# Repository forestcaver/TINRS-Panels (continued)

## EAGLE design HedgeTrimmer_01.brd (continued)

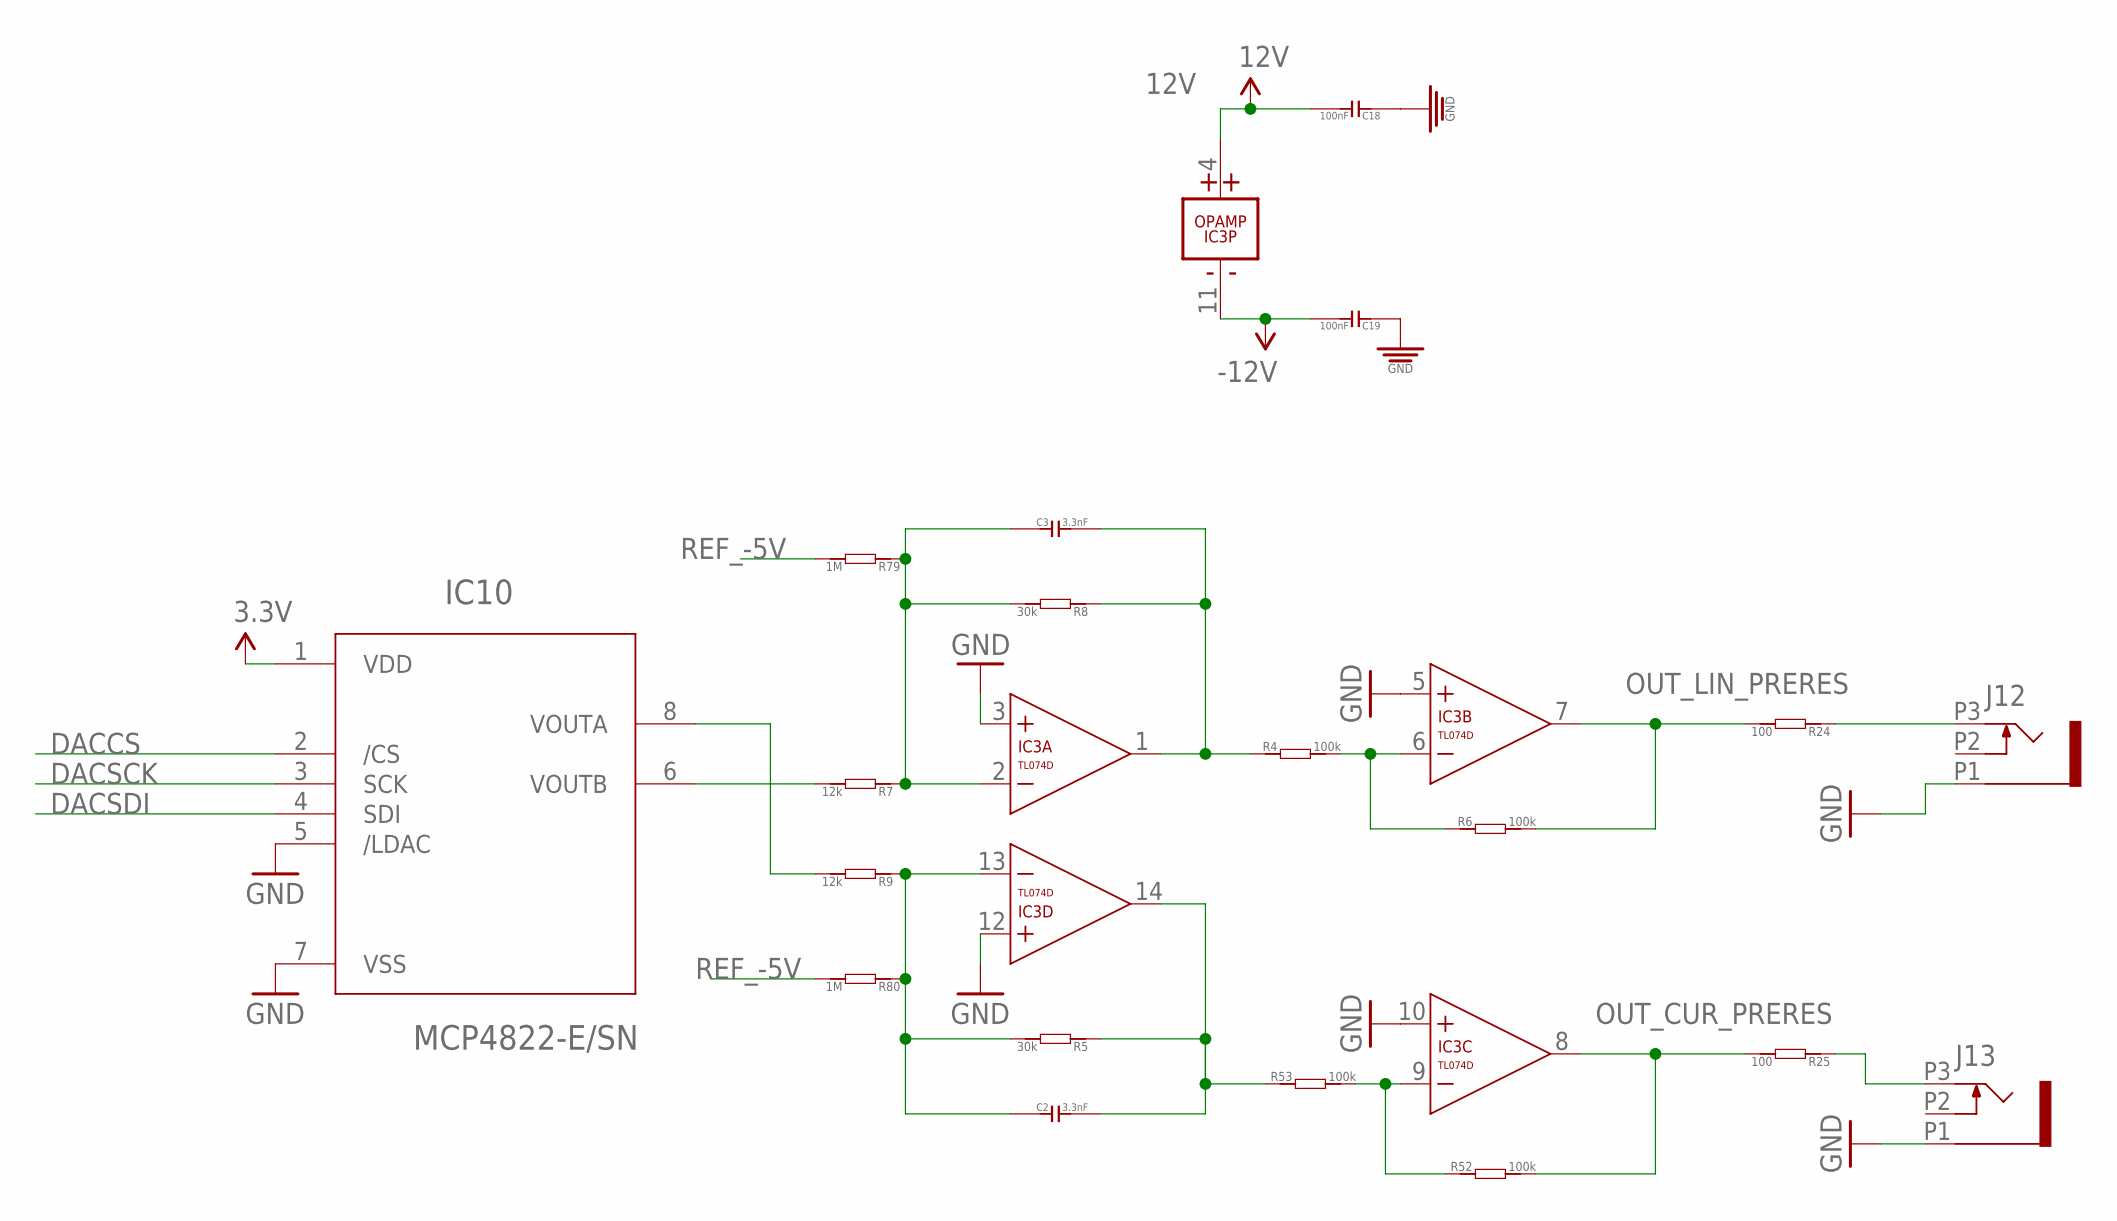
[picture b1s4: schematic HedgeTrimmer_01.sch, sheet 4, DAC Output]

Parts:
C2, C3: 3.3nF; C0603
C18, C19: 100nF; C0603; MPN MC0603F104Z160CT
IC3: TL074D; SO14; MPN TL074CD
IC10: MCP4822-E/SN; SOIC8-N_MC
J12, J13: PJ301_THONKICONN8; WQP_PJ_301M8
R4, R6, R52, R53: 100k; R0603
R5, R8: 30k; R0603
R7, R9: 12k; R0603
R24, R25: 100; R0603
R79, R80: 1M; R0603

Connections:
3.3V: IC10.1 (VDD); also elsewhere on the board
12V: C18.2, IC3.4 (V+); also elsewhere on the board
-12V: C19.2, IC3.11 (V-); also elsewhere on the board
DACA_INPUTSUMMER: C2.1, IC3.13 (-IN), R5.2, R9.1, R80.1
DACB_INPUTSUMMER: C3.1, IC3.2 (-IN), R7.1, R8.2, R79.1
DACCS: IC10.2 (/CS); also elsewhere on the board
DACSCK: IC10.3 (SCK); also elsewhere on the board
DACSDI: IC10.4 (SDI); also elsewhere on the board
GND: C18.1, C19.1, IC3.3 (+IN), IC3.5 (+IN), IC3.10 (+IN), IC3.12 (+IN), IC10.5 (/LDAC), IC10.7 (VSS), J12.P1 (1), J13.P1 (1); also elsewhere on the board
unnamed: IC3.6 (-IN), R4.2, R6.1
unnamed: IC10.8 (VOUTA), R9.2
unnamed: IC10.6 (VOUTB), R7.2
unnamed: J12.P3 (3), R24.1
unnamed: IC3.9 (-IN), R52.1, R53.2
unnamed: C3.2, IC3.1 (OUT), R4.1, R8.1
unnamed: J13.P3 (3), R25.1
unnamed: C2.2, IC3.14 (OUT), R5.1, R53.1
OUT_CUR_PRERES: IC3.8 (OUT), R25.2, R52.2; also elsewhere on the board
OUT_LIN_PRERES: IC3.7 (OUT), R6.2, R24.2
REF_-5V: R79.2, R80.2; also elsewhere on the board

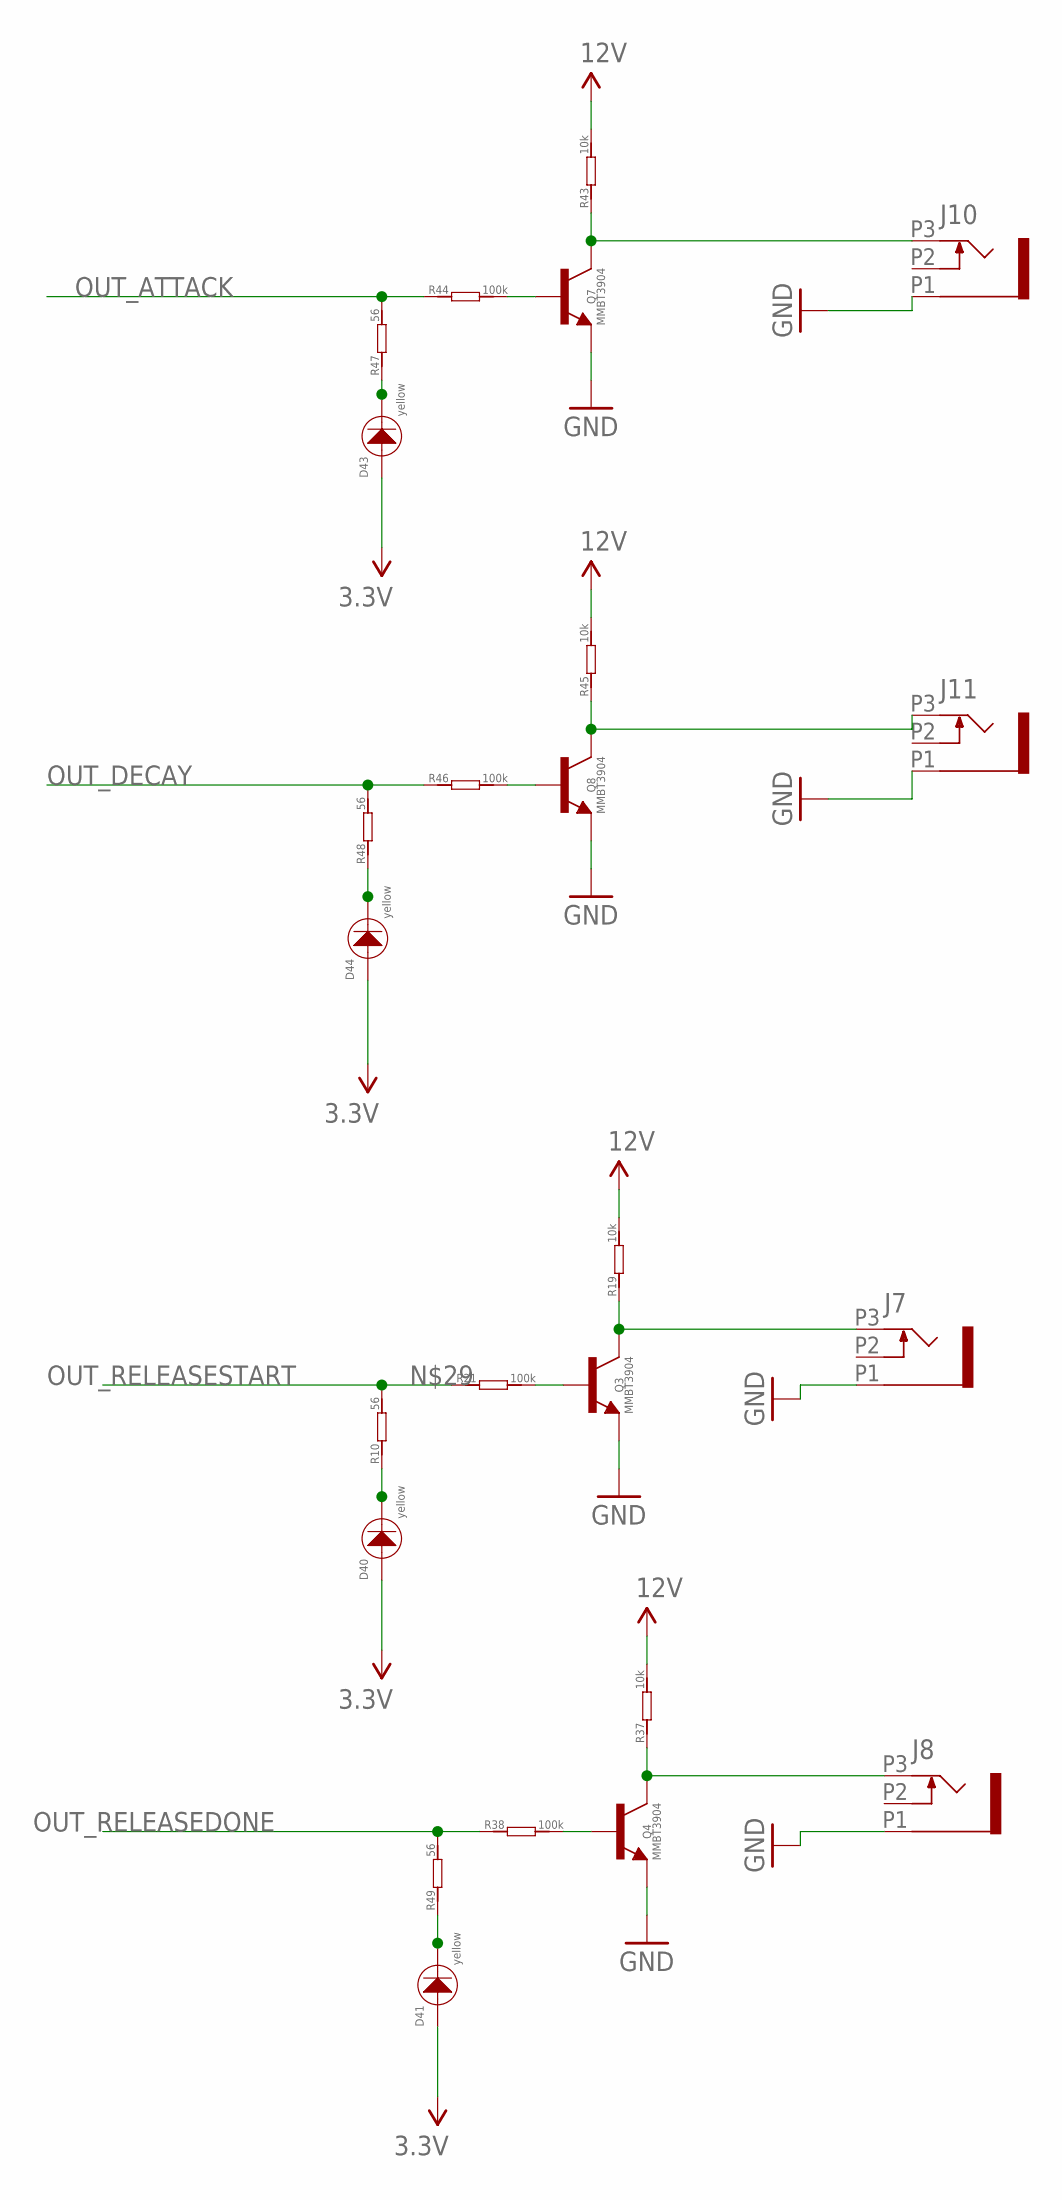
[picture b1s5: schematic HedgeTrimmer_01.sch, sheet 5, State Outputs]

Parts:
D40, D41, D43, D44: yellow; 3MMLED
J7, J8, J10, J11: PJ301_THONKICONN8; WQP_PJ_301M8
Q3, Q4, Q7, Q8: MMBT3904; SOT23-BEC; MPN PMBT3904,215
R10, R47, R48, R49: 56; R0603
R19, R37, R43, R45: 10k; R0603
R21, R38, R44, R46: 100k; R0603

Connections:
3.3V: D40.+, D41.+, D43.+, D44.+; also elsewhere on the board
12V: R19.2, R37.2, R43.2, R45.2; also elsewhere on the board
D21: D43.-, R47.1
GND: J7.P1 (1), J8.P1 (1), J10.P1 (1), J11.P1 (1), Q3.E, Q4.E, Q7.E, Q8.E; also elsewhere on the board
unnamed: D40.-, R10.1
unnamed: Q3.B, R21.2
unnamed: J7.P3 (3), Q3.C, R19.1
unnamed: D41.-, R49.1
unnamed: D44.-, R48.1
unnamed: Q4.B, R38.2
unnamed: J8.P3 (3), Q4.C, R37.1
unnamed: Q7.B, R44.2
unnamed: J10.P3 (3), Q7.C, R43.1
unnamed: Q8.B, R46.2
unnamed: J11.P3 (3), Q8.C, R45.1
OUT_ATTACK: R44.1, R47.2; also elsewhere on the board
OUT_DECAY: R46.1, R48.2; also elsewhere on the board
OUT_RELEASEDONE: R38.1, R49.2; also elsewhere on the board
OUT_RELEASESTART: R10.2, R21.1; also elsewhere on the board

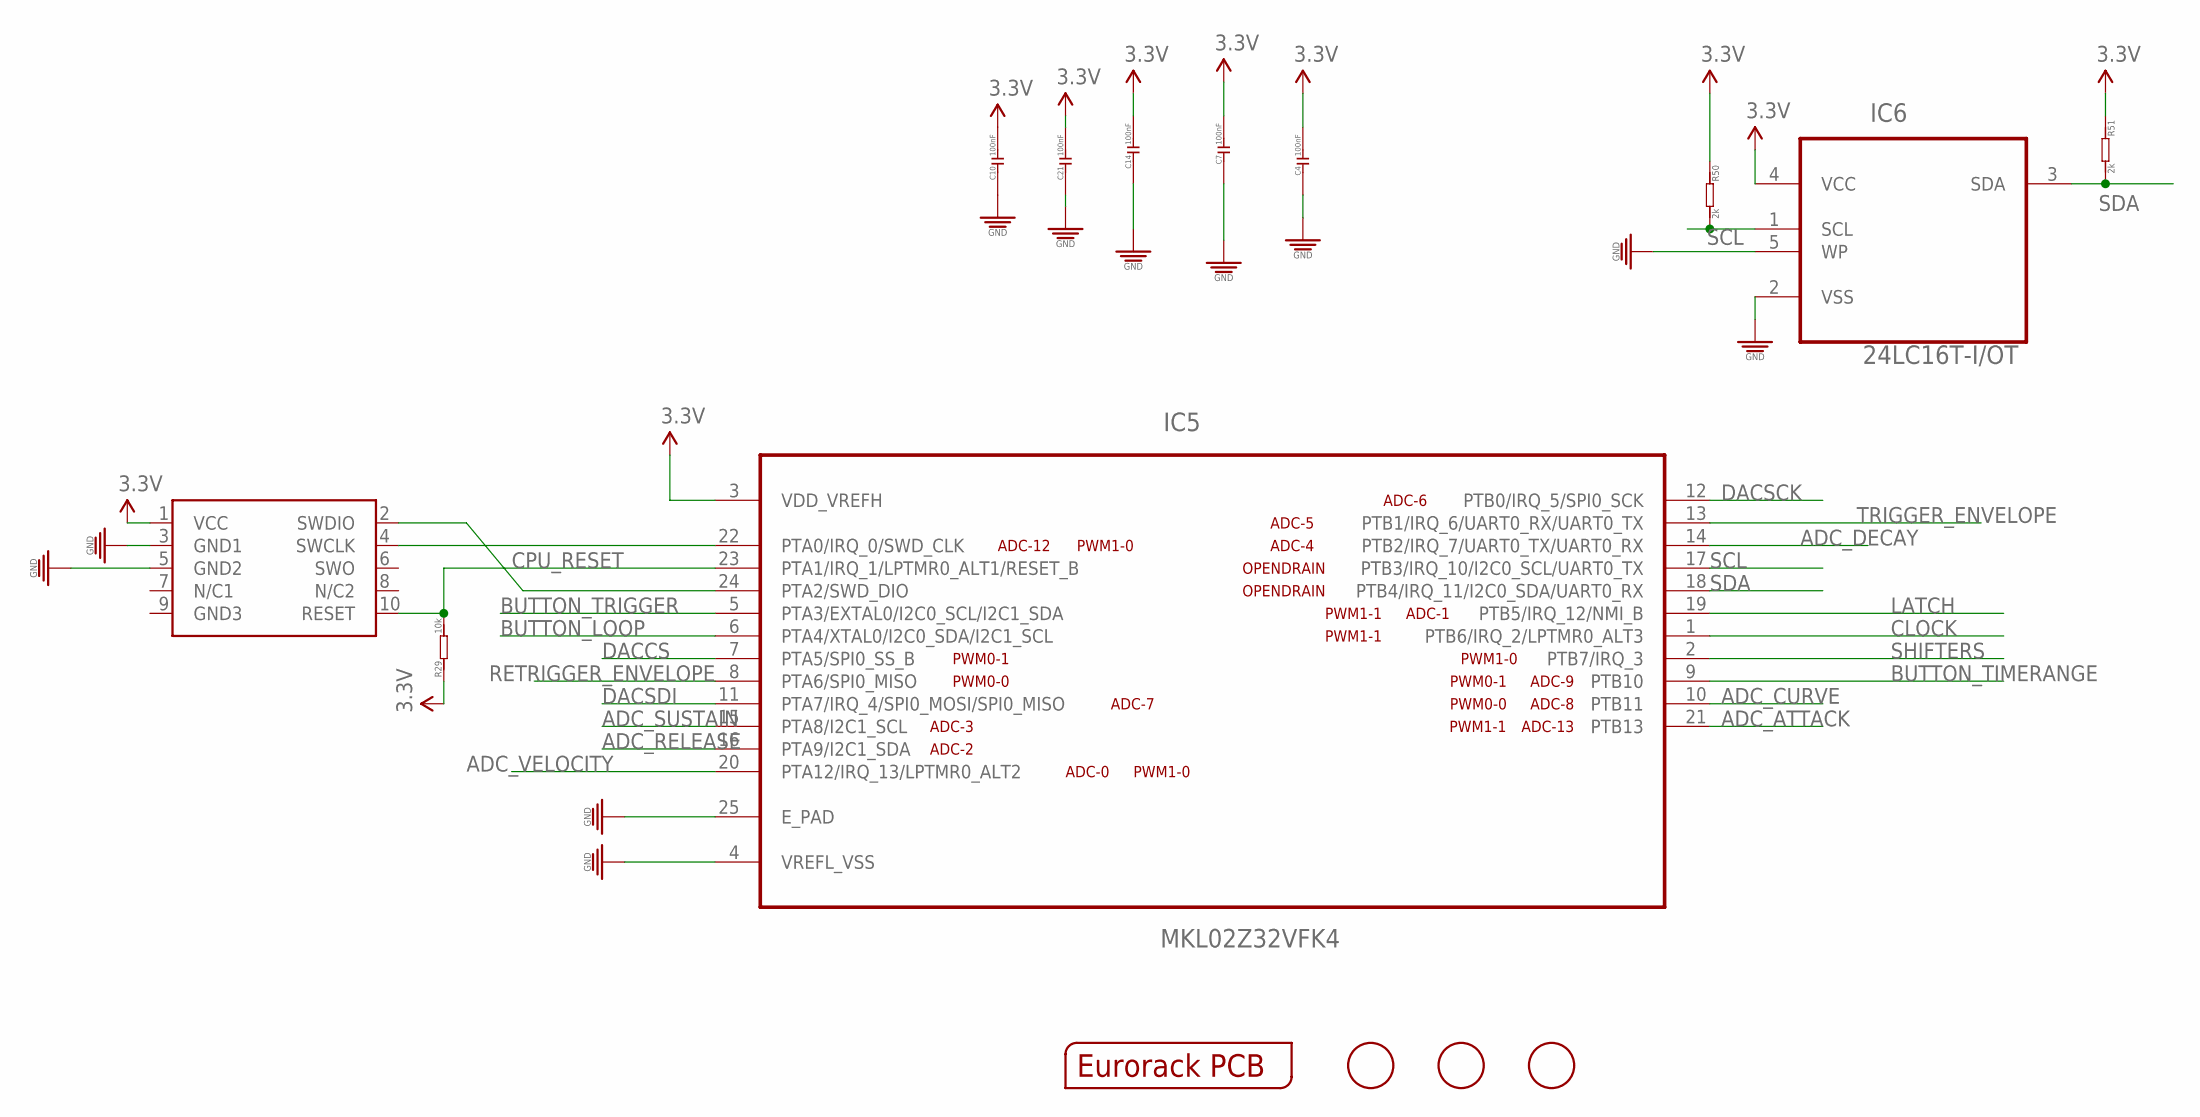
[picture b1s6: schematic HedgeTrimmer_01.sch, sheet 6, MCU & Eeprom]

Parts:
C4, C7, C10, C14, C21: 100nF; C0603; MPN MC0603F104Z160CT
FID1, FID2, FID3: FIDUCIAL; FIDUCIAL_1MM
IC5: MKL02Z32VFK4; QFN50P400X400X100-25N
IC6: 24LC16T-I/OT; SOT95P290X145-5N; MPN 24LC16T-I/OT
OUTLINE: EURORACK_PCB12HP; EURORACK12HPPCB
R29: 10k; R0603
R50, R51: 2k; R0603
SWD1: CORTEX_SWD; M50-3600542

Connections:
3.3V: C4.2, C7.2, C10.2, C14.2, C21.2, IC5.3 (VDD_VREFH), IC6.4 (VCC), R29.1, R50.1, R51.1, SWD1.1 (VCC); also elsewhere on the board
ADC_ATTACK: IC5.21 (PTB13); also elsewhere on the board
ADC_CURVE: IC5.10 (PTB11); also elsewhere on the board
ADC_DECAY: IC5.14 (PTB2/IRQ_7/UART0_TX/UART0_RX); also elsewhere on the board
ADC_RELEASE: IC5.16 (PTA9/I2C1_SDA); also elsewhere on the board
ADC_SUSTAIN: IC5.15 (PTA8/I2C1_SCL); also elsewhere on the board
ADC_VELOCITY: IC5.20 (PTA12/IRQ_13/LPTMR0_ALT2); also elsewhere on the board
BUTTON_LOOP: IC5.6 (PTA4/XTAL0/I2C0_SDA/I2C1_SCL); also elsewhere on the board
BUTTON_TIMERANGE: IC5.9 (PTB10); also elsewhere on the board
BUTTON_TRIGGER: IC5.5 (PTA3/EXTAL0/I2C0_SCL/I2C1_SDA); also elsewhere on the board
CLOCK: IC5.1 (PTB6/IRQ_2/LPTMR0_ALT3); also elsewhere on the board
CPU_RESET: IC5.23 (PTA1/IRQ_1/LPTMR0_ALT1/RESET_B), R29.2, SWD1.10 (RESET)
DACCS: IC5.7 (PTA5/SPI0_SS_B); also elsewhere on the board
DACSCK: IC5.12 (PTB0/IRQ_5/SPI0_SCK); also elsewhere on the board
DACSDI: IC5.11 (PTA7/IRQ_4/SPI0_MOSI/SPI0_MISO); also elsewhere on the board
GND: C4.1, C7.1, C10.1, C14.1, C21.1, IC5.4 (VREFL_VSS), IC5.25 (E_PAD), IC6.2 (VSS), IC6.5 (WP), SWD1.3 (GND1), SWD1.5 (GND2); also elsewhere on the board
LATCH: IC5.19 (PTB5/IRQ_12/NMI_B); also elsewhere on the board
RETRIGGER_ENVELOPE: IC5.8 (PTA6/SPI0_MISO); also elsewhere on the board
SCL: IC5.17 (PTB3/IRQ_10/I2C0_SCL/UART0_TX), IC6.1 (SCL), R50.2
SDA: IC5.18 (PTB4/IRQ_11/I2C0_SDA/UART0_RX), IC6.3 (SDA), R51.2
SHIFTERS: IC5.2 (PTB7/IRQ_3); also elsewhere on the board
SWD_CLK: IC5.22 (PTA0/IRQ_0/SWD_CLK), SWD1.4 (SWCLK)
SWD_DIO: IC5.24 (PTA2/SWD_DIO), SWD1.2 (SWDIO)
TRIGGER_ENVELOPE: IC5.13 (PTB1/IRQ_6/UART0_RX/UART0_TX); also elsewhere on the board

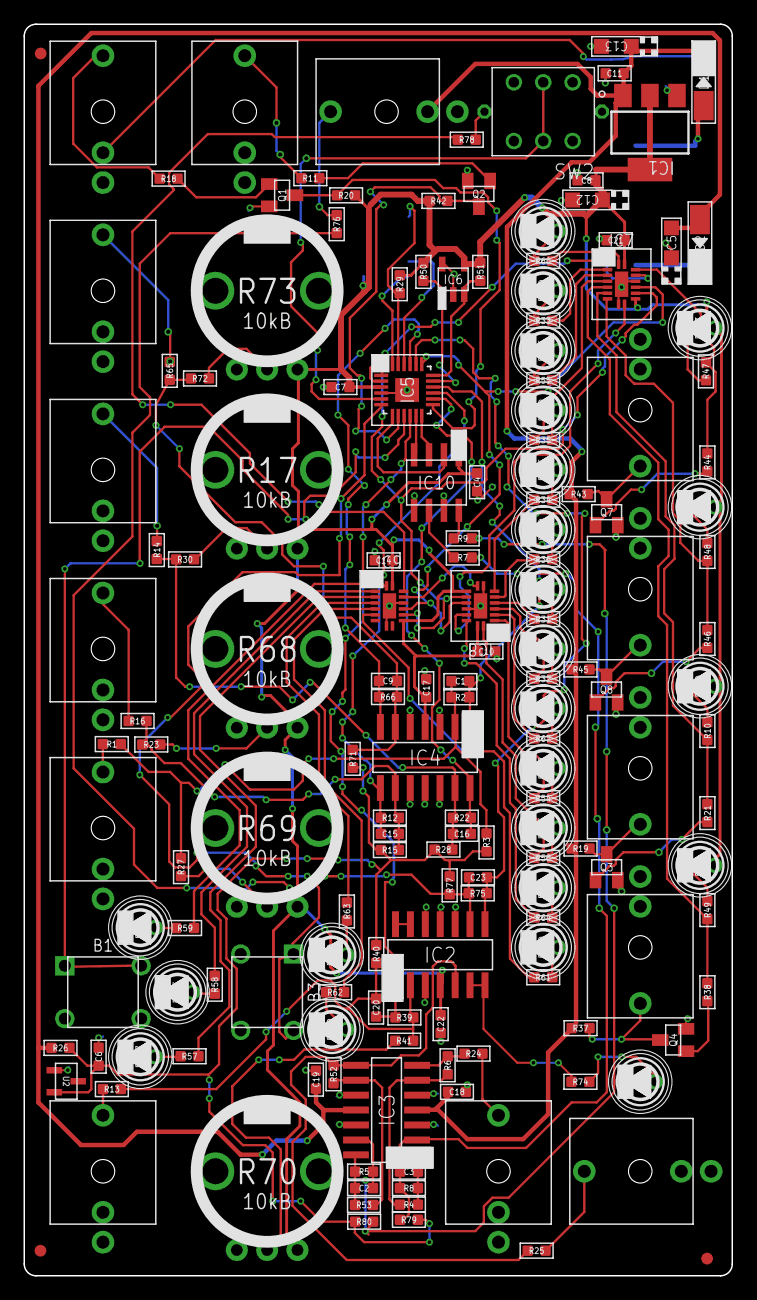
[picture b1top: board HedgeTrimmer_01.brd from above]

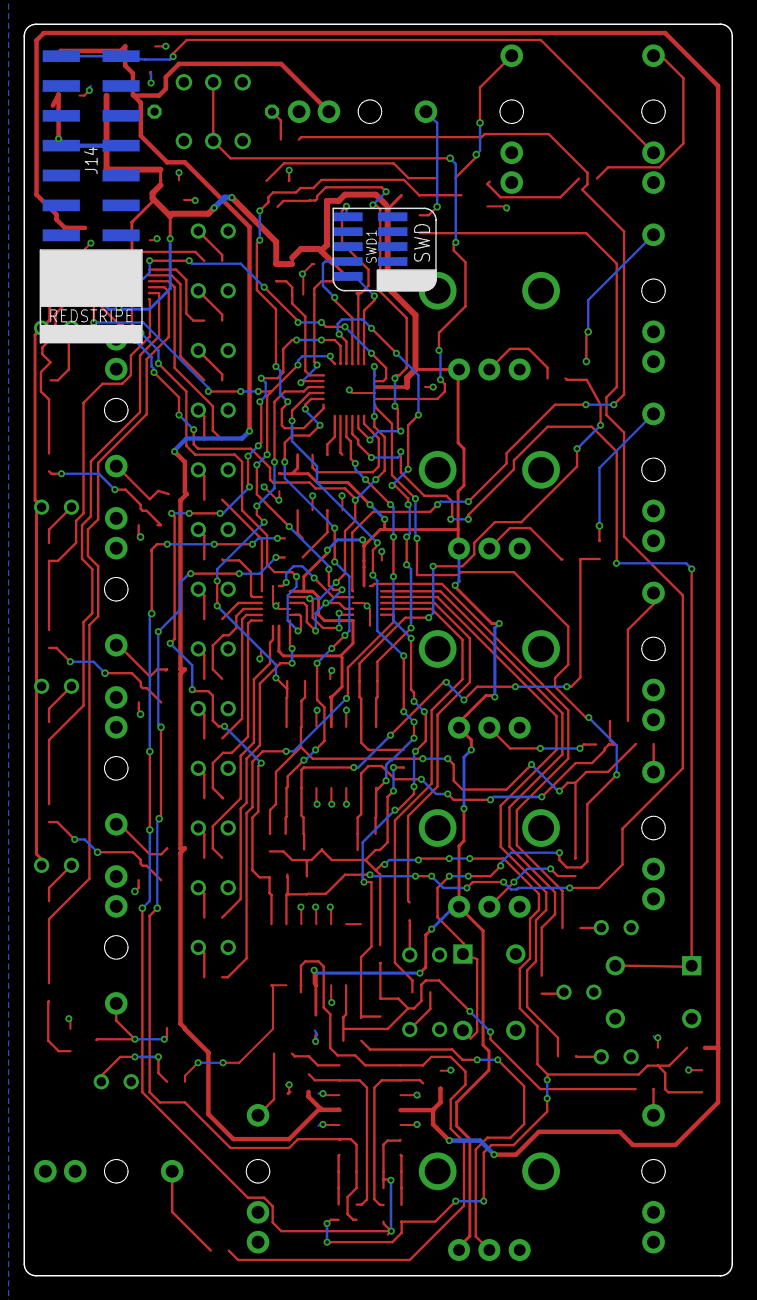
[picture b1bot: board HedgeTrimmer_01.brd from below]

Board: 2 copper layers, 60.2 x 106.5 mm, 168 parts (2 on the bottom side), 122 nets.

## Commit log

2019-09-17 HedgeTrimmer (Edgecutter) panel
